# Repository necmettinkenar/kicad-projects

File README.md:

# KiCad projects with automated CI/CD using KiBot

GitHub Actions + KiBot ile otomatik:
- **DRC** (Design Rule Check) — PCB tasarım kural kontrolleri
- **ERC** (Electrical Rule Check) — Elektriksel kural kontrolleri
- **Gerber** — Üretim dosyaları (Gerber X2 + job file)
- **Drill** — Excellon drill + IPC-2581
- **BOM** — Bill of Materials (HTML + CSV)
- **Pick & Place** — Montaj dosyası (CSV, mm)
- **PCB PDF** — Renkli PCB layout çıktısı
- **Şematik PDF** — Şematik çıktısı
- **3D Render** — SVG formatında 3D görselleştirme
- **3D STEP** — STEP formatında 3D model

## Kullanım

1. KiCad projelerini `projects/` klasörüne koy
2. Commit ve push yap
3. GitHub Actions KiBot ile DRC/ERC çalıştırır
4. main branch'ine push'ta tüm üretim dosyaları otomatik üretilir
5. Çıktılar Actions artifacts olarak indirilir

## Klasör Yapısı

```
kicad-projects/
├── .github/workflows/
│   └── kicad-ci.yml           # KiBot CI/CD pipeline
├── kibot.yml                   # KiBot yapılandırması
├── projects/                   # KiCad projelerin buraya
├── scripts/
│   └── pre-commit-check.py    # Lokal pre-commit DRC/ERC
└── README.md
```

## Lokalde KiBot Kullanımı

```bash
# KiBot kurulu (KiCad Python ile)
"C:\Program Files\KiCad\10.0\bin\Scripts\kibot.exe" -b projects/proje/proje.kicad_pcb -e projects/proje/proje.kicad_sch -c kibot.yml -d output -v
```

## CI/CD Pipeline

| Aşama | Tetikleyici | Çıktı |
|-------|-------------|-------|
| DRC + ERC | Her push/PR | Hata raporu (txt) |
| Manufacturing | main branch push | Gerber, Drill, BOM, PnP |
| Documentation | main branch push | PCB PDF, Şematik PDF, 3D SVG |
| 3D Model | main branch push | STEP dosyası |

## Gereksinimler

- KiCad 10.0 (lokalde)
- GitHub Actions (otomatik, ek kurulum yok)
- KiBot 1.9.1 (CI container'da hazır, lokalde KiCad Python ile)

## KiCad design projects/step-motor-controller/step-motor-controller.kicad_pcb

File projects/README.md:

# projects/

KiCad projelerini bu klasöre koy.

Her proje kendi alt klasöründe olmalı:

```
projects/
├── led-blinker/
│   ├── led-blinker.kicad_pro
│   ├── led-blinker.kicad_sch
│   ├── led-blinker.kicad_pcb
│   └── led-blinker.kicad_prl
├── power-supply/
│   ├── power-supply.kicad_pro
│   ├── power-supply.kicad_sch
│   └── power-supply.kicad_pcb
```

Bir proje eklediğinde commit + push yap, CI/CD otomatik çalışır.

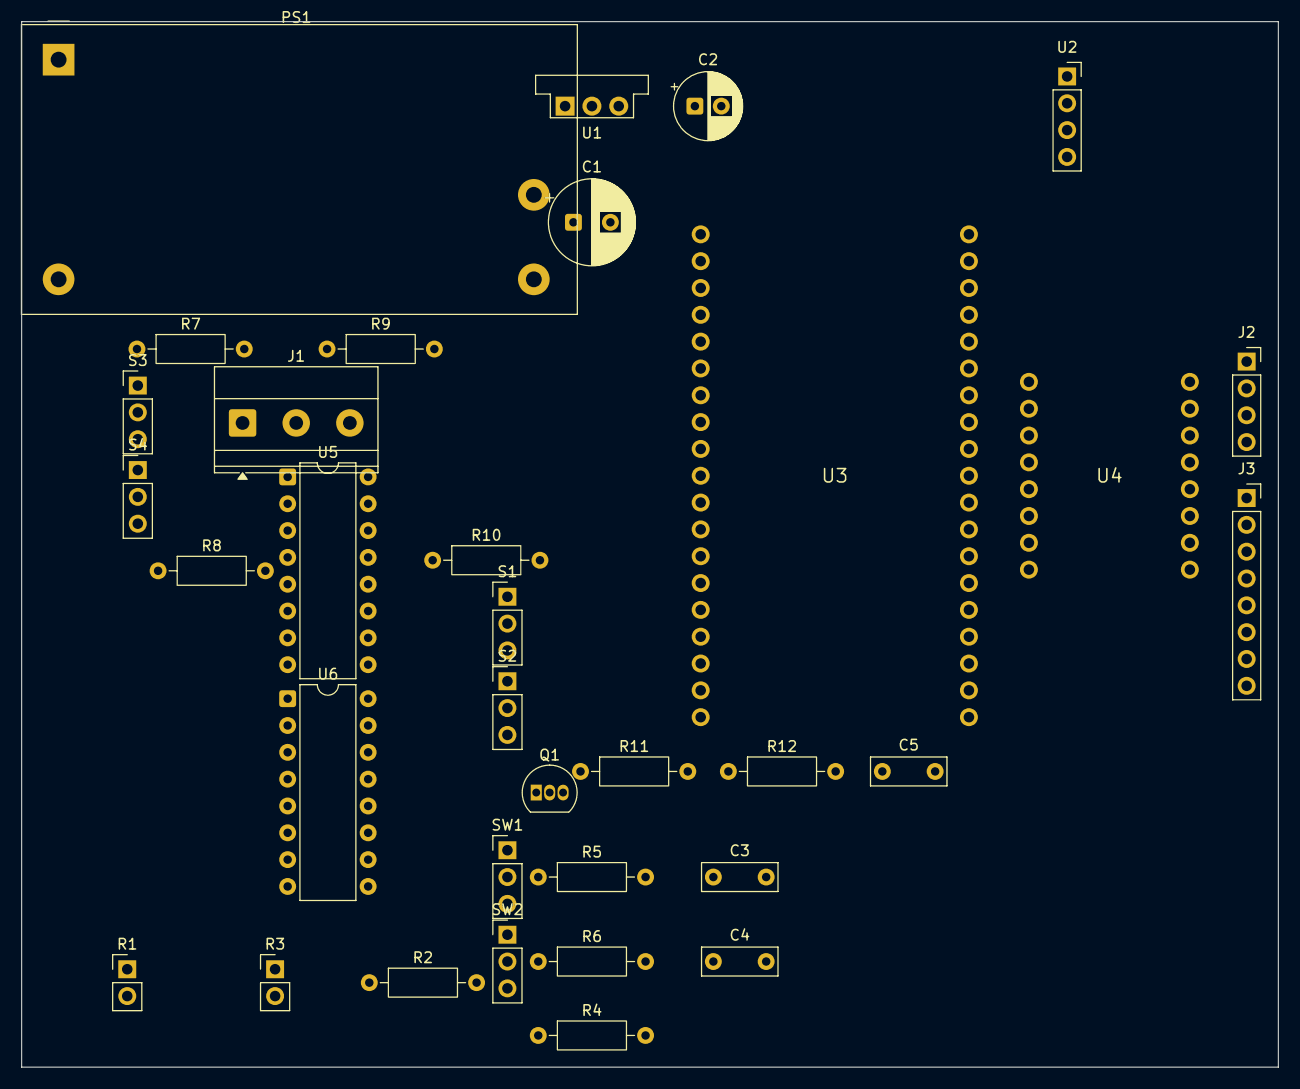
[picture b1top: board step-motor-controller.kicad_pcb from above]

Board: 2 copper layers, 119.0 x 99.0 mm, 34 parts (0 on the bottom side), 45 nets, no tracks yet.

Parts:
C1: C1; CP_Radial_D8.0mm_P3.50mm
C2: C2; CP_Radial_D6.3mm_P2.50mm
C3: C3; C_Rect_L7.0mm_W2.5mm_P5.00mm
C4: C4; C_Rect_L7.0mm_W2.5mm_P5.00mm
C5: C5; C_Rect_L7.0mm_W2.5mm_P5.00mm
J1: AC Input; TerminalBlock_Phoenix_MKDS-1,5-3-5.08_1x03_P5.08mm_Horizont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
J2: Motor; PinSocket_1x04_P2.54mm_Vertical
J3: Encoder; PinSocket_1x08_P2.54mm_Vertical
PS1: IRM-20-24; Converter_ACDC_MeanWell_IRM-20-xx_THT
Q1: BC547; TO-92_Inline
R1: R1; PinHeader_1x02_P2.54mm_Vertical
R2: R2; R_Axial_DIN0207_L6.3mm_D2.5mm_P10.16mm_Horizontal
R3: R3; PinHeader_1x02_P2.54mm_Vertical
R4: R4; R_Axial_DIN0207_L6.3mm_D2.5mm_P10.16mm_Horizontal
R5: R5; R_Axial_DIN0207_L6.3mm_D2.5mm_P10.16mm_Horizontal
R6: R6; R_Axial_DIN0207_L6.3mm_D2.5mm_P10.16mm_Horizontal
R7: R7; R_Axial_DIN0207_L6.3mm_D2.5mm_P10.16mm_Horizontal
R8: R8; R_Axial_DIN0207_L6.3mm_D2.5mm_P10.16mm_Horizontal
R9: R9; R_Axial_DIN0207_L6.3mm_D2.5mm_P10.16mm_Horizontal
R10: R10; R_Axial_DIN0207_L6.3mm_D2.5mm_P10.16mm_Horizontal
R11: R11; R_Axial_DIN0207_L6.3mm_D2.5mm_P10.16mm_Horizontal
R12: R12; R_Axial_DIN0207_L6.3mm_D2.5mm_P10.16mm_Horizontal
S1: S1; PinHeader_1x03_P2.54mm_Vertical
S2: S2; PinHeader_1x03_P2.54mm_Vertical
S3: S3; PinHeader_1x03_P2.54mm_Vertical
S4: S4; PinHeader_1x03_P2.54mm_Vertical
SW1: SW1; PinHeader_1x03_P2.54mm_Vertical
SW2: SW2; PinHeader_1x03_P2.54mm_Vertical
U1: OKI-78SR-5; Converter_DCDC_Murata_OKI-78SR_Vertical
U2: UART Display; PinSocket_1x04_P2.54mm_Vertical
U3: ESP32-DevKitC
U4: LV8729
U5: AM26LS32ACN; DIP-16_W7.62mm
U6: 74HC4050N; DIP-16_W7.62mm

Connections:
+3V3: R1.1, R3.1, R5.2, R6.2, R11.1, U3.1
+5V: C2.1, J3.1, S1.1, S2.1, S3.1, S4.1, U1.3, U2.1, U3.19, U4.10, U5.4, U5.16, U6.1
+24V: C1.1, PS1.4, U1.1, U4.16
AC_L: J1.1, PS1.1
AC_N: J1.2, PS1.2
CHIP_PU: C5.1, Q1.1, R11.2, U3.2
ENC_A_BUF: U5.3, U6.3
ENC_A_N: J3.4, U5.1
ENC_A_P: J3.3, U5.2
ENC_B_BUF: U5.5, U6.5
ENC_B_N: J3.6, U5.6
ENC_B_P: J3.5, U5.7
ENC_Z_BUF: U5.11, U6.7
ENC_Z_ESP: U3.15, U6.6
ENC_Z_N: J3.8, U5.10
ENC_Z_P: J3.7, U5.9
FSR1_TOP: R1.2, R2.1, U3.7
FSR2_TOP: R3.2, R4.1, U3.8
GND: C1.2, C2.2, C3.2, C4.2, C5.2, J1.3, J3.2, PS1.3, Q1.3, R2.2, R4.2, R8.1, R10.1, S1.3, S2.3, S3.2, S4.2, SW1.2, SW2.2, U1.2, U2.4, U3.14, U4.9, U4.15, U5.8, U5.12, U6.8
GPIO18_OPTIC1: U3.30, U6.10
GPIO19_OPTIC2: U3.31, U6.12
GPIO21_ENC_A: U3.32, U6.2
GPIO22_ENC_B: U3.33, U6.4
GPIO23_RST: R12.1, U3.37
HALL1_DIV: R7.2, R8.2, U3.5
HALL1_RAW: R7.1, S3.3
HALL2_DIV: R9.2, R10.2, U3.6
HALL2_RAW: R9.1, S4.3
MOT_1A: J2.1, U4.14
MOT_1B: J2.2, U4.13
MOT_2A: J2.3, U4.12
MOT_2B: J2.4, U4.11
M_DIR: U3.11, U4.8
M_EN: U3.12, U4.1
M_MS1: U3.26, U4.2
M_MS2: U3.29, U4.3
M_MS3: U3.9, U4.4
M_STEP: U3.10, U4.7
OPTIC1_RAW: S1.2, U6.9
OPTIC2_RAW: S2.2, U6.11
Q1_BASE: Q1.2, R12.2
SW1_SIG: C3.1, R5.1, SW1.1, U3.3
SW2_SIG: C4.1, R6.1, SW2.1, U3.4
UART_M_RX: U2.3, U3.28
UART_M_TX: U2.2, U3.27

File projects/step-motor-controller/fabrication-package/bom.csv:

"Refs","Value","Footprint","Qty","DNP"
"C1","100uF/35V","Capacitor_THT:CP_Radial_D8.0mm_P3.50mm","1",""
"C2","10uF/16V","Capacitor_THT:CP_Radial_D6.3mm_P2.50mm","1",""
"C3","100nF","Capacitor_THT:C_Rect_L7.0mm_W2.5mm_P5.00mm","1",""
"C4","100nF","Capacitor_THT:C_Rect_L7.0mm_W2.5mm_P5.00mm","1",""
"C5","100nF","Capacitor_THT:C_Rect_L7.0mm_W2.5mm_P5.00mm","1",""
"J1","AC Input","TerminalBlock_Phoenix:TerminalBlock_Phoenix_MKDS-1,5-3-5.08_1x03_P5.08mm_Horizontal","1",""
"J2","Step Motor","Connector_PinSocket_2.54mm:PinSocket_1x04_P2.54mm_Vertical","1",""
"J3","Encoder","Connector_PinSocket_2.54mm:PinSocket_1x08_P2.54mm_Vertical","1",""
"PS1","IRM-20-24","Converter_ACDC:Converter_ACDC_MeanWell_IRM-20-xx_THT","1",""
"Q1","BC547","Package_TO_SOT_THT:TO-92_Inline","1",""
"R1","FSR (external)","Connector_PinHeader_2.54mm:PinHeader_1x02_P2.54mm_Vertical","1",""
"R2","10K","Resistor_THT:R_Axial_DIN0207_L6.3mm_D2.5mm_P10.16mm_Horizontal","1",""
"R3","FSR (external)","Connector_PinHeader_2.54mm:PinHeader_1x02_P2.54mm_Vertical","1",""
"R4","10K","Resistor_THT:R_Axial_DIN0207_L6.3mm_D2.5mm_P10.16mm_Horizontal","1",""
"R5","10K","Resistor_THT:R_Axial_DIN0207_L6.3mm_D2.5mm_P10.16mm_Horizontal","1",""
"R6","10K","Resistor_THT:R_Axial_DIN0207_L6.3mm_D2.5mm_P10.16mm_Horizontal","1",""
"R7","10K","Resistor_THT:R_Axial_DIN0207_L6.3mm_D2.5mm_P10.16mm_Horizontal","1",""
"R8","20K","Resistor_THT:R_Axial_DIN0207_L6.3mm_D2.5mm_P10.16mm_Horizontal","1",""
"R9","10K","Resistor_THT:R_Axial_DIN0207_L6.3mm_D2.5mm_P10.16mm_Horizontal","1",""
"R10","20K","Resistor_THT:R_Axial_DIN0207_L6.3mm_D2.5mm_P10.16mm_Horizontal","1",""
"R11","10K","Resistor_THT:R_Axial_DIN0207_L6.3mm_D2.5mm_P10.16mm_Horizontal","1",""
"R12","1K","Resistor_THT:R_Axial_DIN0207_L6.3mm_D2.5mm_P10.16mm_Horizontal","1",""
"S1","Optic LS-1","Connector_PinHeader_2.54mm:PinHeader_1x03_P2.54mm_Vertical","1",""
"S2","Optic LS-2","Connector_PinHeader_2.54mm:PinHeader_1x03_P2.54mm_Vertical","1",""
"S3","Hall-1","Connector_PinHeader_2.54mm:PinHeader_1x03_P2.54mm_Vertical","1",""
"S4","Hall-2","Connector_PinHeader_2.54mm:PinHeader_1x03_P2.54mm_Vertical","1",""
"SW1","SW1","Connector_PinHeader_2.54mm:PinHeader_1x03_P2.54mm_Vertical","1",""
"SW2","SW2","Connector_PinHeader_2.54mm:PinHeader_1x03_P2.54mm_Vertical","1",""
"U1","OKI-78SR-5","Converter_DCDC:Converter_DCDC_Murata_OKI-78SR_Vertical","1",""
"U2","UART Display","Connector_PinSocket_2.54mm:PinSocket_1x04_P2.54mm_Vertical","1",""
"U3","ESP32-DevKitC","AUTO:ESP32_SOCKET","1",""
"U4","LV8729 Module","AUTO:STEPSTICK_2x8","1",""
"U5","AM26LS32ACN","Package_DIP:DIP-16_W7.62mm","1",""
"U6","74HC4050N","Package_DIP:DIP-16_W7.62mm","1",""

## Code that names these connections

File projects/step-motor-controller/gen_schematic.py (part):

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    34:'NC',35:'NC',36:'NC',37:'GPIO23',38:'NC'}
U3_MAP = {1:'+3V3',2:'CHIP_PU',3:'SW1_SIG',4:'SW2_SIG',5:'HALL1_DIV',6:'HALL2_DIV',7:'FSR1_TOP',
    8:'FSR2_TOP',9:'M_MS3',10:'M_STEP',11:'M_DIR',12:'M_EN',14:'GND',15:'ENC_Z_ESP',19:'+5V',
    26:'M_MS1',27:'UART_M_TX',28:'UART_M_RX',29:'M_MS2',30:'GPIO18_OPTIC1',31:'GPIO19_OPTIC2',
    32:'GPIO21_ENC_A',33:'GPIO22_ENC_B',37:'GPIO23_RST'}
u3_pins = []
for n in range(1, 39):
    et = 'free' if U3_NAMES[n] == 'NC' else ('power_out' if n == 1 else ('power_in' if n in (14, 19) else ('input' if n == 2 else 'bidirectional')))
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
U6_NAMES = {1:'VCC',2:'1Y',3:'1A',4:'2Y',5:'2A',6:'3Y',7:'3A',8:'GND',9:'4A',10:'4Y',11:'5A',
    12:'5Y',13:'6A',14:'6Y',15:'NC',16:'NC'}
U6_MAP = {1:'+5V',2:'GPIO21_ENC_A',3:'ENC_A_BUF',4:'GPIO22_ENC_B',5:'ENC_B_BUF',6:'ENC_Z_ESP',
    7:'ENC_Z_BUF',8:'GND',9:'OPTIC1_RAW',10:'GPIO18_OPTIC1',11:'OPTIC2_RAW',12:'GPIO19_OPTIC2'}
u6_pins = [(str(n), U6_NAMES[n], 'free' if n in (15, 16) else ('power_in' if n in (1, 8) else 'passive')) for n in range(1, 17)]

U1_MAP = {1:'+24V', 2:'GND', 3:'+5V'}
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    ('U5',  'KicadAuto', 'AM26LS32ACN', 'AM26LS32ACN', 'Package_DIP:DIP-16_W7.62mm', U5_MAP),
    ('U6',  'KicadAuto', '74HC4050', '74HC4050N_652', 'Package_DIP:DIP-16_W7.62mm', U6_MAP),
    ('Q1',  'Transistor_BJT', 'BC547', 'BC547', 'Package_TO_SOT_THT:TO-92_Inline', 'BY_BJT'),
    ('R1',  'Connector_Generic', 'Conn_01x02', 'FSR (external)', 'Connector_PinHeader_2.54mm:PinHeader_1x02_P2.54mm_Vertical', {1:'+3V3', 2:'FSR1_TOP'}),
    ('R2',  'Device', 'R', '10K', 'Resistor_SMD:R_0805_2012Metric', {1:'FSR1_TOP', 2:'GND'}),
    ('R3',  'Connector_Generic', 'Conn_01x02', 'FSR (external)', 'Connector_PinHeader_2.54mm:PinHeader_1x02_P2.54mm_Vertical', {1:'+3V3', 2:'FSR2_TOP'}),
    ('R4',  'Device', 'R', '10K', 'Resistor_SMD:R_0805_2012Metric', {1:'FSR2_TOP', 2:'GND'}),
    ('R5',  'Device', 'R', '10K', 'Resistor_SMD:R_0805_2012Metric', {1:'SW1_SIG', 2:'+3V3'}),
    ('R6',  'Device', 'R', '10K', 'Resistor_SMD:R_0805_2012Metric', {1:'SW2_SIG', 2:'+3V3'}),
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    ('R9',  'Device', 'R', '10K', 'Resistor_SMD:R_0805_2012Metric', {1:'HALL2_RAW', 2:'HALL2_DIV'}),
    ('R10', 'Device', 'R', '20K', 'Resistor_SMD:R_0805_2012Metric', {1:'GND', 2:'HALL2_DIV'}),
    ('R11', 'Device', 'R', '10K', 'Resistor_SMD:R_0805_2012Metric', {1:'+3V3', 2:'CHIP_PU'}),
    ('R12', 'Device', 'R', '1K', 'Resistor_SMD:R_0805_2012Metric', {1:'GPIO23_RST', 2:'Q1_BASE'}),
    ('C1',  'Device', 'C_Polarized', '100uF/35V', 'Capacitor_THT:CP_Radial_D6.3mm_P2.50mm', {1:'+24V', 2:'GND'}),
    ('C2',  'Device', 'C_Polarized', '10uF/16V', 'Capacitor_THT:CP_Radial_D5.0mm_P2.50mm', {1:'+5V', 2:'GND'}),
    ('C3',  'Device', 'C', '100nF', 'Capacitor_SMD:C_0805_2012Metric', {1:'SW1_SIG', 2:'GND'}),
    ('C4',  'Device', 'C', '100nF', 'Capacitor_SMD:C_0805_2012Metric', {1:'SW2_SIG', 2:'GND'}),
    ('C5',  'Device', 'C', '100nF', 'Capacitor_SMD:C_0805_2012Metric', {1:'CHIP_PU', 2:'GND'}),
    ('S1',  'Connector_Generic', 'Conn_01x03', 'Optic LS-1', 'Connector_PinHeader_2.54mm:PinHeader_1x03_P2.54mm_Vertical', {1:'+5V', 2:'OPTIC1_RAW', 3:'GND'}),
    ('S2',  'Connector_Generic', 'Conn_01x03', 'Optic LS-2', 'Connector_PinHeader_2.54mm:PinHeader_1x03_P2.54mm_Vertical', {1:'+5V', 2:'OPTIC2_RAW', 3:'GND'}),
    ('S3',  'Connector_Generic', 'Conn_01x03', 'Hall-1', 'Connector_PinHeader_2.54mm:PinHeader_1x03_P2.54mm_Vertical', {1:'+5V', 2:'GND', 3:'HALL1_RAW'}),
    ('S4',  'Connector_Generic', 'Conn_01x03', 'Hall-2', 'Connector_PinHeader_2.54mm:PinHeader_1x03_P2.54mm_Vertical', {1:'+5V', 2:'GND', 3:'HALL2_RAW'}),
    ('SW1', 'Switch', 'SW_SPDT', 'Limit SW-1', 'Connector_PinHeader_2.54mm:PinHeader_1x03_P2.54mm_Vertical', {1:'SW1_SIG', 2:'GND'}),
    ('SW2', 'Switch', 'SW_SPDT', 'Limit SW-2', 'Connector_PinHeader_2.54mm:PinHeader_1x03_P2.54mm_Vertical', {1:'SW2_SIG', 2:'GND'}),
]

# schematic positions (centers)
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
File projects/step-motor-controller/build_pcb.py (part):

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
ORDER = ['MOT_1A', 'MOT_1B', 'MOT_2A', 'MOT_2B',
         'ENC_A_P', 'ENC_A_N', 'ENC_B_P', 'ENC_B_N', 'ENC_Z_P', 'ENC_Z_N',
         'ENC_A_BUF', 'ENC_B_BUF', 'ENC_Z_BUF', 'GPIO21_ENC_A', 'GPIO22_ENC_B', 'ENC_Z_ESP',
         'GPIO18_OPTIC1', 'GPIO19_OPTIC2', 'OPTIC1_RAW', 'OPTIC2_RAW',
         'UART_M_TX', 'UART_M_RX',
         'M_EN', 'M_MS1', 'M_MS2', 'M_MS3', 'M_STEP', 'M_DIR', 'GPIO23_RST',
         'SW1_SIG', 'SW2_SIG', 'HALL1_RAW', 'HALL1_DIV', 'HALL2_RAW', 'HALL2_DIV',
         'FSR1_TOP', 'FSR2_TOP',
         '+24V', '+3V3', '+5V']
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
